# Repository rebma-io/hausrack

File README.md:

# HAUSRACK

This has [been moved to Codeberg](https://codeberg.org/petrilli/hausrack-website).

A wildly over-engineered home automation project

* License: CERN-OHL-S

Features
--------

* TODO

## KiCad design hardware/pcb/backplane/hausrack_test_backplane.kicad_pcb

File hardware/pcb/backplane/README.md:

# HAUSRACK Test Backplane

More details on the
[update](https://hausrack.rebma.io/updates/2024/05/02/a-bus-is-a-bus-of-course-of-course/).

## Design Principles

When I was looking at how [kha](https://github.com/kiu/kha/) structured
the bus, I decided to pull a few ideas from what they did:

1. Leverage DIN 41612 for the physical format of the bus. This is a very
   well understood and documented specification, and it has been
   battle-tested over many decades.
2. Simplify the backplane routing requirement.
3. Carry both +12V and +5V. Can be locally regulated down to the needed
   voltage.

## Physical Connector

I decided to use the DIN 41612 connector because it is an absolute tank.
It has been used, at least, since the late 1980s in dozens and dozens of
critical systems. It's also relatively inexpensive and not very finicky
to work with.

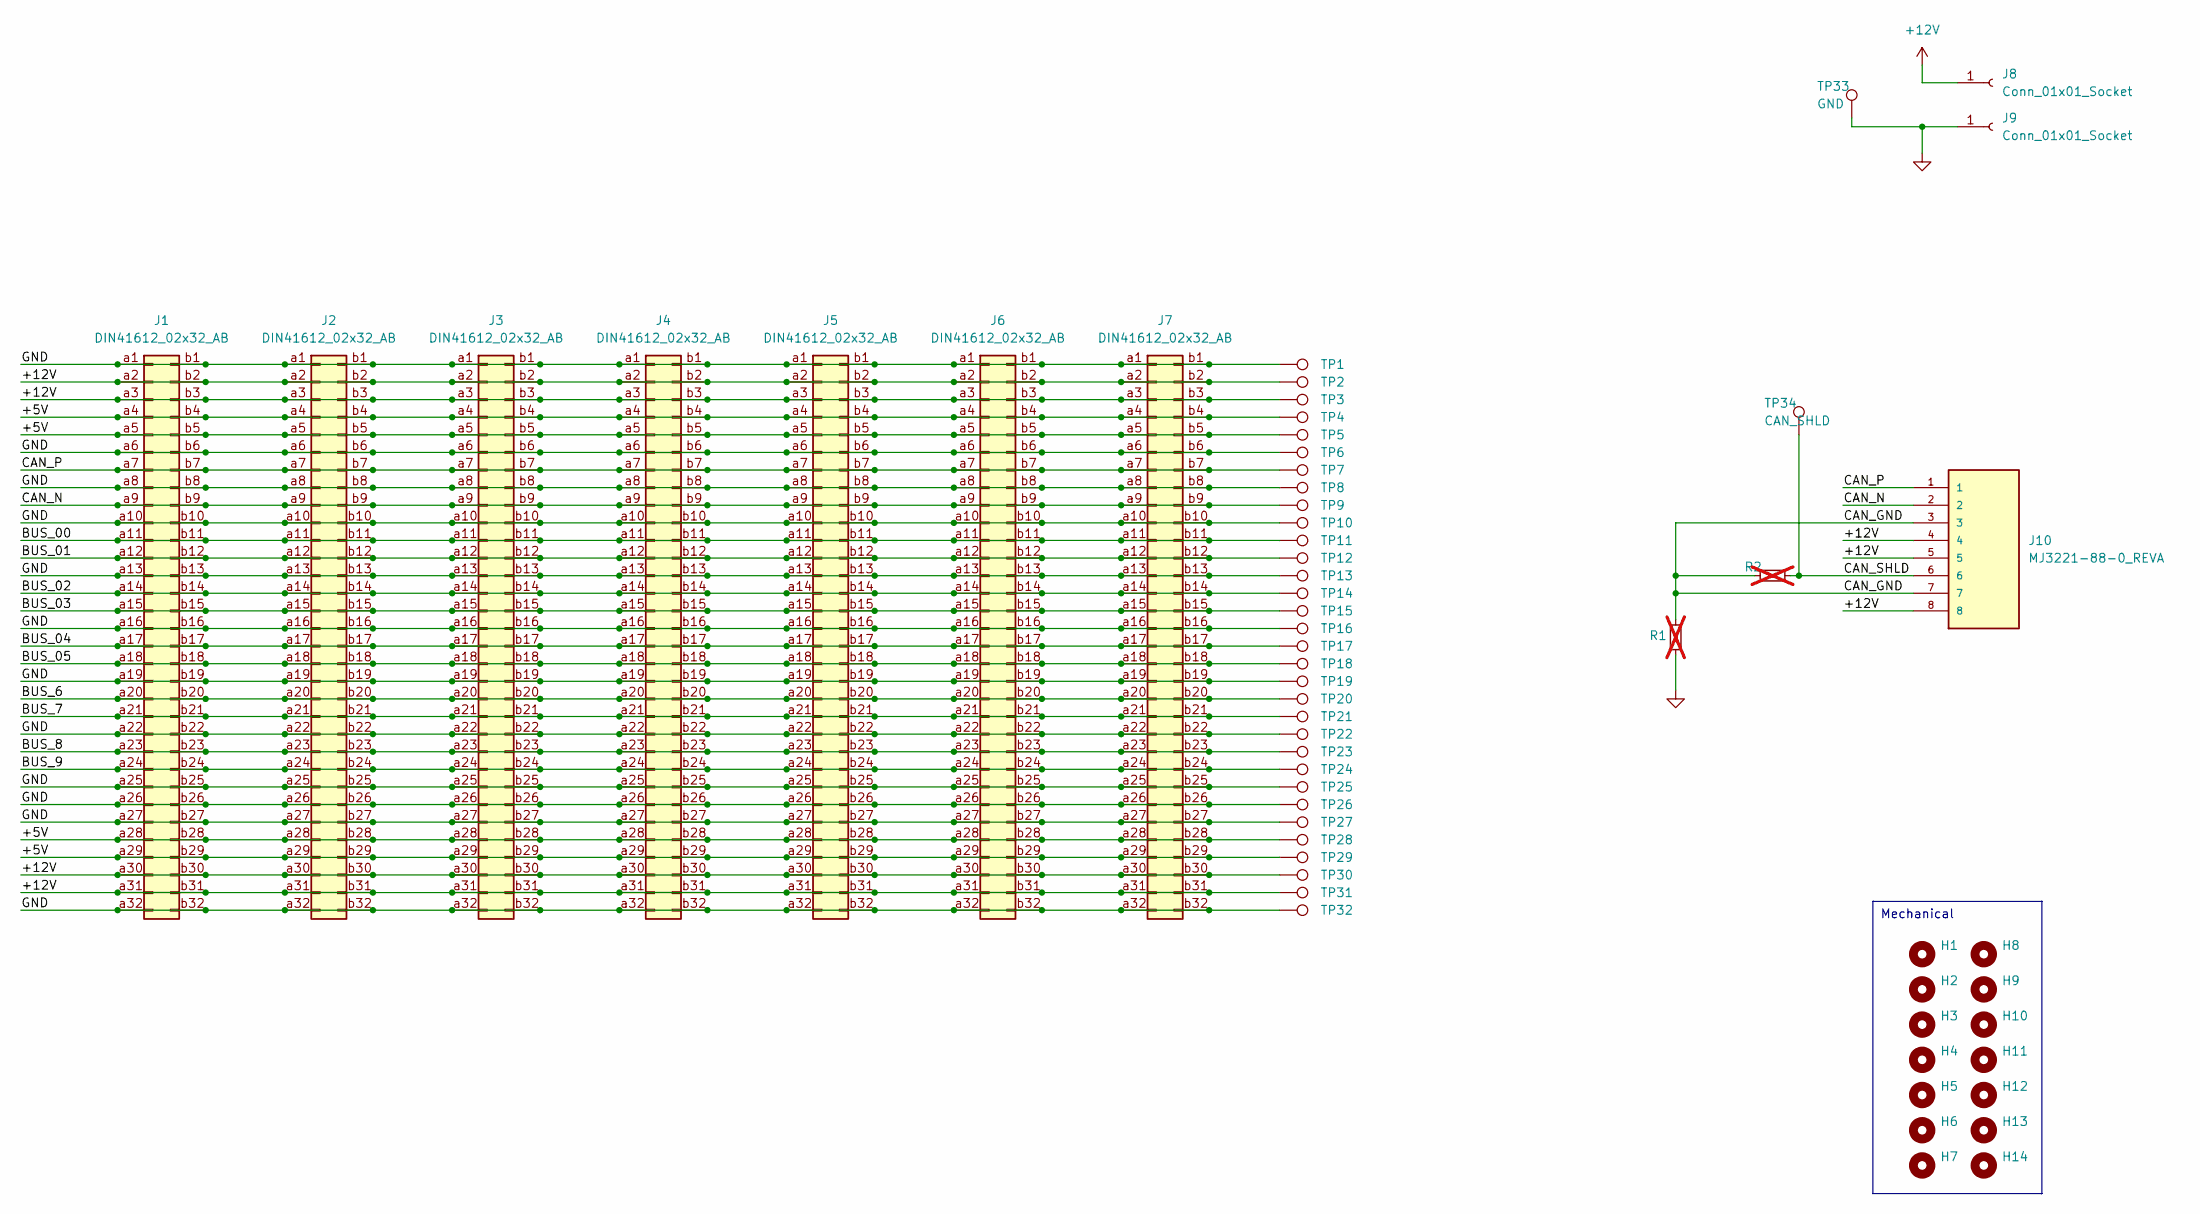
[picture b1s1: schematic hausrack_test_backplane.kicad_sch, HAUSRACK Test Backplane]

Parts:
H1, H2, H3, H4, H5, H6, H7, H8, H9, H10, H11, H12, H13, H14: MountingHole; MountingHole_2.7mm_M2.5_DIN965
J1, J2, J3, J4, J5, J6, J7: DIN41612_02x32_AB; DIN41612_B_2x32_Female_Vertical_THT
J8, J9: Conn_01x01_Socket; Banana_Cliff_FCR7350B_S16N-PC_Horizontal
J10: MJ3221-88-0_REVA; GCT_MJ3221-88-0_REVA; PARTREV A
R1, R2: 0R; R_0603_1608Metric_Pad0.98x0.95mm_HandSolder; not fitted
TP1, TP2, TP3, TP4, TP5, TP6, TP7, TP8, TP9, TP10, TP11, TP12, TP13, TP14, TP15, TP16, TP17, TP18, TP19, TP20, TP21, TP22, TP23, TP24, TP25, TP26, TP27, TP28, TP29, TP30, TP31, TP32: TestPoint; TestPoint_Pad_1.0x1.0mm
TP33: GND; TestPoint_Loop_D2.54mm_Drill1.5mm_Beaded
TP34: CAN_SHLD; TestPoint_Loop_D2.54mm_Drill1.5mm_Beaded

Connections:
+12V: J1.a2, J1.a3, J1.a30, J1.a31, J1.b2, J1.b3, J1.b30, J1.b31, J2.a2, J2.a3, J2.a30, J2.a31, J2.b2, J2.b3, J2.b30, J2.b31, J3.a2, J3.a3, J3.a30, J3.a31, J3.b2, J3.b3, J3.b30, J3.b31, J4.a2, J4.a3, J4.a30, J4.a31, J4.b2, J4.b3, J4.b30, J4.b31, J5.a2, J5.a3, J5.a30, J5.a31, J5.b2, J5.b3, J5.b30, J5.b31, J6.a2, J6.a3, J6.a30, J6.a31, J6.b2, J6.b3, J6.b30, J6.b31, J7.a2, J7.a3, J7.a30, J7.a31, J7.b2, J7.b3, J7.b30, J7.b31, J8.1, J10.4, J10.5, J10.8, TP2.1, TP3.1, TP30.1, TP31.1
/+5V: J1.a4, J1.a5, J1.a28, J1.a29, J1.b4, J1.b5, J1.b28, J1.b29, J2.a4, J2.a5, J2.a28, J2.a29, J2.b4, J2.b5, J2.b28, J2.b29, J3.a4, J3.a5, J3.a28, J3.a29, J3.b4, J3.b5, J3.b28, J3.b29, J4.a4, J4.a5, J4.a28, J4.a29, J4.b4, J4.b5, J4.b28, J4.b29, J5.a4, J5.a5, J5.a28, J5.a29, J5.b4, J5.b5, J5.b28, J5.b29, J6.a4, J6.a5, J6.a28, J6.a29, J6.b4, J6.b5, J6.b28, J6.b29, J7.a4, J7.a5, J7.a28, J7.a29, J7.b4, J7.b5, J7.b28, J7.b29, TP4.1, TP5.1, TP28.1, TP29.1
/BUS_00: J1.a11, J1.b11, J2.a11, J2.b11, J3.a11, J3.b11, J4.a11, J4.b11, J5.a11, J5.b11, J6.a11, J6.b11, J7.a11, J7.b11, TP11.1
/BUS_01: J1.a12, J1.b12, J2.a12, J2.b12, J3.a12, J3.b12, J4.a12, J4.b12, J5.a12, J5.b12, J6.a12, J6.b12, J7.a12, J7.b12, TP12.1
/BUS_02: J1.a14, J1.b14, J2.a14, J2.b14, J3.a14, J3.b14, J4.a14, J4.b14, J5.a14, J5.b14, J6.a14, J6.b14, J7.a14, J7.b14, TP14.1
/BUS_03: J1.a15, J1.b15, J2.a15, J2.b15, J3.a15, J3.b15, J4.a15, J4.b15, J5.a15, J5.b15, J6.a15, J6.b15, J7.a15, J7.b15, TP15.1
/BUS_04: J1.a17, J1.b17, J2.a17, J2.b17, J3.a17, J3.b17, J4.a17, J4.b17, J5.a17, J5.b17, J6.a17, J6.b17, J7.a17, J7.b17, TP17.1
/BUS_05: J1.a18, J1.b18, J2.a18, J2.b18, J3.a18, J3.b18, J4.a18, J4.b18, J5.a18, J5.b18, J6.a18, J6.b18, J7.a18, J7.b18, TP18.1
/BUS_6: J1.a20, J1.b20, J2.a20, J2.b20, J3.a20, J3.b20, J4.a20, J4.b20, J5.a20, J5.b20, J6.a20, J6.b20, J7.a20, J7.b20, TP20.1
/BUS_7: J1.a21, J1.b21, J2.a21, J2.b21, J3.a21, J3.b21, J4.a21, J4.b21, J5.a21, J5.b21, J6.a21, J6.b21, J7.a21, J7.b21, TP21.1
/BUS_8: J1.a23, J1.b23, J2.a23, J2.b23, J3.a23, J3.b23, J4.a23, J4.b23, J5.a23, J5.b23, J6.a23, J6.b23, J7.a23, J7.b23, TP23.1
/BUS_9: J1.a24, J1.b24, J2.a24, J2.b24, J3.a24, J3.b24, J4.a24, J4.b24, J5.a24, J5.b24, J6.a24, J6.b24, J7.a24, J7.b24, TP24.1
/CAN_GND: J10.3, J10.7, R1.2, R2.1
/CAN_N: J1.a9, J1.b9, J2.a9, J2.b9, J3.a9, J3.b9, J4.a9, J4.b9, J5.a9, J5.b9, J6.a9, J6.b9, J7.a9, J7.b9, J10.2, TP9.1
/CAN_P: J1.a7, J1.b7, J2.a7, J2.b7, J3.a7, J3.b7, J4.a7, J4.b7, J5.a7, J5.b7, J6.a7, J6.b7, J7.a7, J7.b7, J10.1, TP7.1
/CAN_SHLD: J10.6, R2.2, TP34.1
GND: J1.a1, J1.a6, J1.a8, J1.a10, J1.a13, J1.a16, J1.a19, J1.a22, J1.a25, J1.a26, J1.a27, J1.a32, J1.b1, J1.b6, J1.b8, J1.b10, J1.b13, J1.b16, J1.b19, J1.b22, J1.b25, J1.b26, J1.b27, J1.b32, J2.a1, J2.a6, J2.a8, J2.a10, J2.a13, J2.a16, J2.a19, J2.a22, J2.a25, J2.a26, J2.a27, J2.a32, J2.b1, J2.b6, J2.b8, J2.b10, J2.b13, J2.b16, J2.b19, J2.b22, J2.b25, J2.b26, J2.b27, J2.b32, J3.a1, J3.a6, J3.a8, J3.a10, J3.a13, J3.a16, J3.a19, J3.a22, J3.a25, J3.a26, J3.a27, J3.a32, J3.b1, J3.b6, J3.b8, J3.b10, J3.b13, J3.b16, J3.b19, J3.b22, J3.b25, J3.b26, J3.b27, J3.b32, J4.a1, J4.a6, J4.a8, J4.a10, J4.a13, J4.a16, J4.a19, J4.a22, J4.a25, J4.a26, J4.a27, J4.a32, J4.b1, J4.b6, J4.b8, J4.b10, J4.b13, J4.b16, J4.b19, J4.b22, J4.b25, J4.b26, J4.b27, J4.b32, J5.a1, J5.a6, J5.a8, J5.a10, J5.a13, J5.a16, J5.a19, J5.a22, J5.a25, J5.a26, J5.a27, J5.a32, J5.b1, J5.b6, J5.b8, J5.b10, J5.b13, J5.b16, J5.b19, J5.b22, J5.b25, J5.b26, J5.b27, J5.b32, J6.a1, J6.a6, J6.a8, J6.a10, J6.a13, J6.a16, J6.a19, J6.a22, J6.a25, J6.a26, J6.a27, J6.a32, J6.b1, J6.b6, J6.b8, J6.b10, J6.b13, J6.b16, J6.b19, J6.b22, J6.b25, J6.b26, J6.b27, J6.b32, J7.a1, J7.a6, J7.a8, J7.a10, J7.a13, J7.a16, J7.a19, J7.a22, J7.a25, J7.a26, J7.a27, J7.a32, J7.b1, J7.b6, J7.b8, J7.b10, J7.b13, J7.b16, J7.b19, J7.b22, J7.b25, J7.b26, J7.b27, J7.b32, J9.1, R1.1, TP1.1, TP6.1, TP8.1, TP10.1, TP13.1, TP16.1, TP19.1, TP22.1, TP25.1, TP26.1, TP27.1, TP32.1, TP33.1

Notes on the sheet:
Mechanical

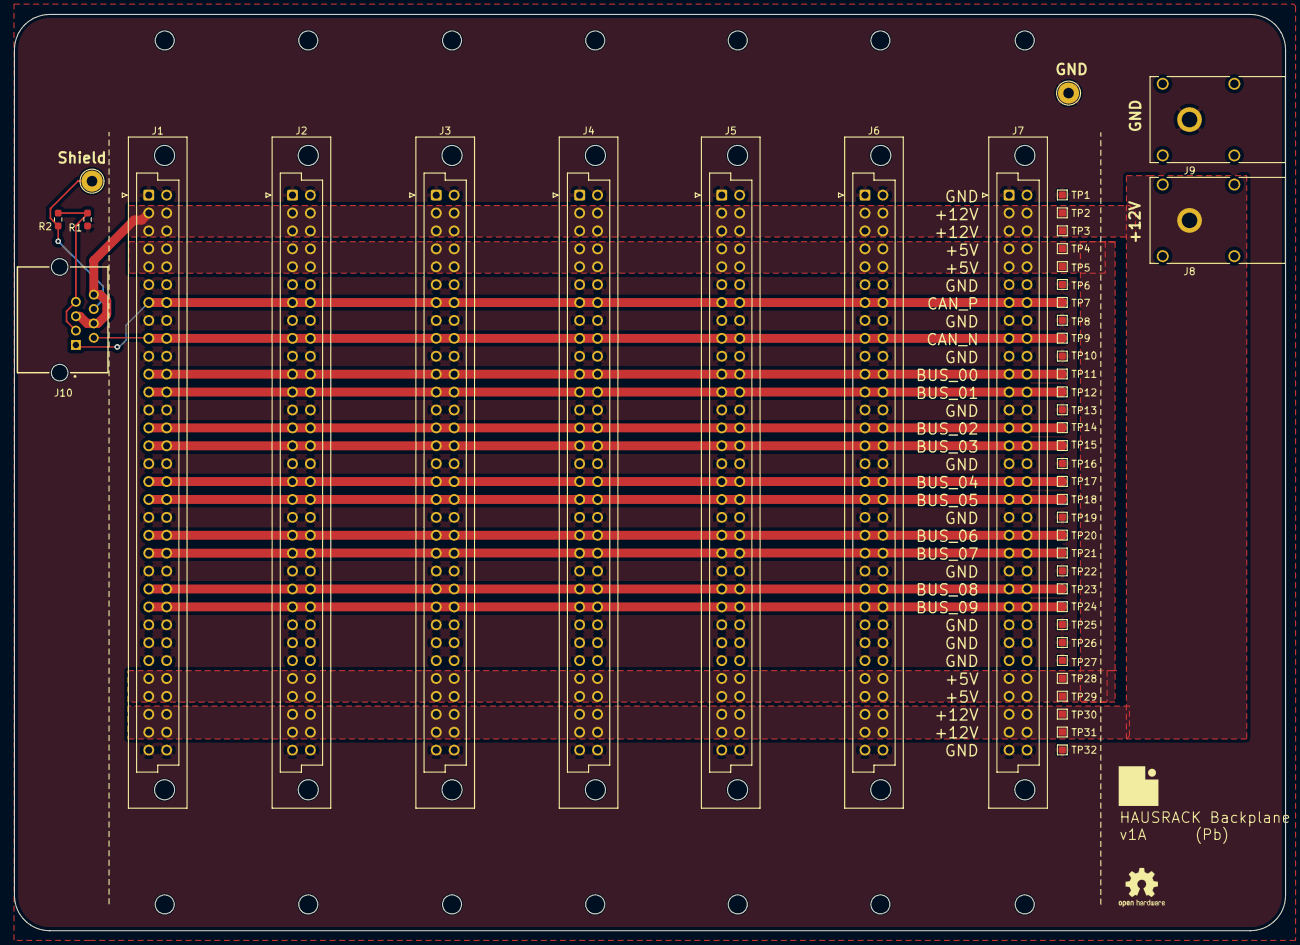
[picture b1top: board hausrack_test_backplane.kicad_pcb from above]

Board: 2 copper layers, 180.3 x 130.0 mm, 60 parts (0 on the bottom side), 17 nets.

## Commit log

2024-04-23 Cookiecutter generated base project
2024-04-23 build(git):
    Ignore IntelliJ nonsense.
2024-04-23 build(poetry): Initial dependency lock.
2024-04-23 build(ci): Remove Poetry cache
    Running into build issues with Github actions, so trying it without the Poetry cache.
2024-04-23 build(ci): Update action versions
2024-04-23 build(git): Change dependency
    Can't use the git dependency URL.
2024-04-23 build(git): Tweak action versions
2024-04-23 build(make): Add ghdocs target
2024-04-23 ci(action): Run Makefile version of ghdocs
2024-04-23 build(make): Update makefile
2024-04-23 build(git): Add Python to gitignore
2024-04-23 docs(logo): Add logo for project
2024-05-02 Initial entry for the public
2024-05-03 Quick writeup on initial backplane design.
2024-05-03 Initial v1A backplane
2024-05-03 Quick readme
2024-05-03 Add link to GitHub PCB
2024-05-03 Add stupid CNAME file
2024-05-04 Writeup on connector
2024-05-04 Minor tweak to see if Github builds them correctly.
2024-05-04 Move CNAME into docs directory
2024-05-04 Continued struggle with Wireviz
2024-05-04 Install graphviz in the Action
2024-05-04 Pin the Python version in the Action
2024-05-04 Update dependencies
2024-05-05 Write-up of the "base board" thoughts
2024-05-05 Undraft the post!
2024-05-06 Added some small analytics provided by Fathom
    These are privacy preserving and do not reveal any detailed information. See https://usefathom.com/ for more information.
2024-05-14 Post: First oscillation
2024-05-17 Oh no
2024-05-17 Deployed 846ef6a with MkDocs version: 1.6.0
2024-08-18 New post on board setup in Zephyr
2024-08-18 Add picture of the board
2024-08-25 Writeup of development board
2024-08-25 Minor wording change
2024-08-25 Draft of post on creepage
2024-09-09 Add note about published repo
2024-09-09 Deployed 7b83b9b with MkDocs version: 1.6.0
2025-08-12 Deployed fe3f914 with MkDocs version: 1.6.0
